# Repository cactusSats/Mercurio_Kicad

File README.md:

# Mercúrio_Kicad
Kicad, Gerbers e arquivos Flatcam do satélite mercúrio

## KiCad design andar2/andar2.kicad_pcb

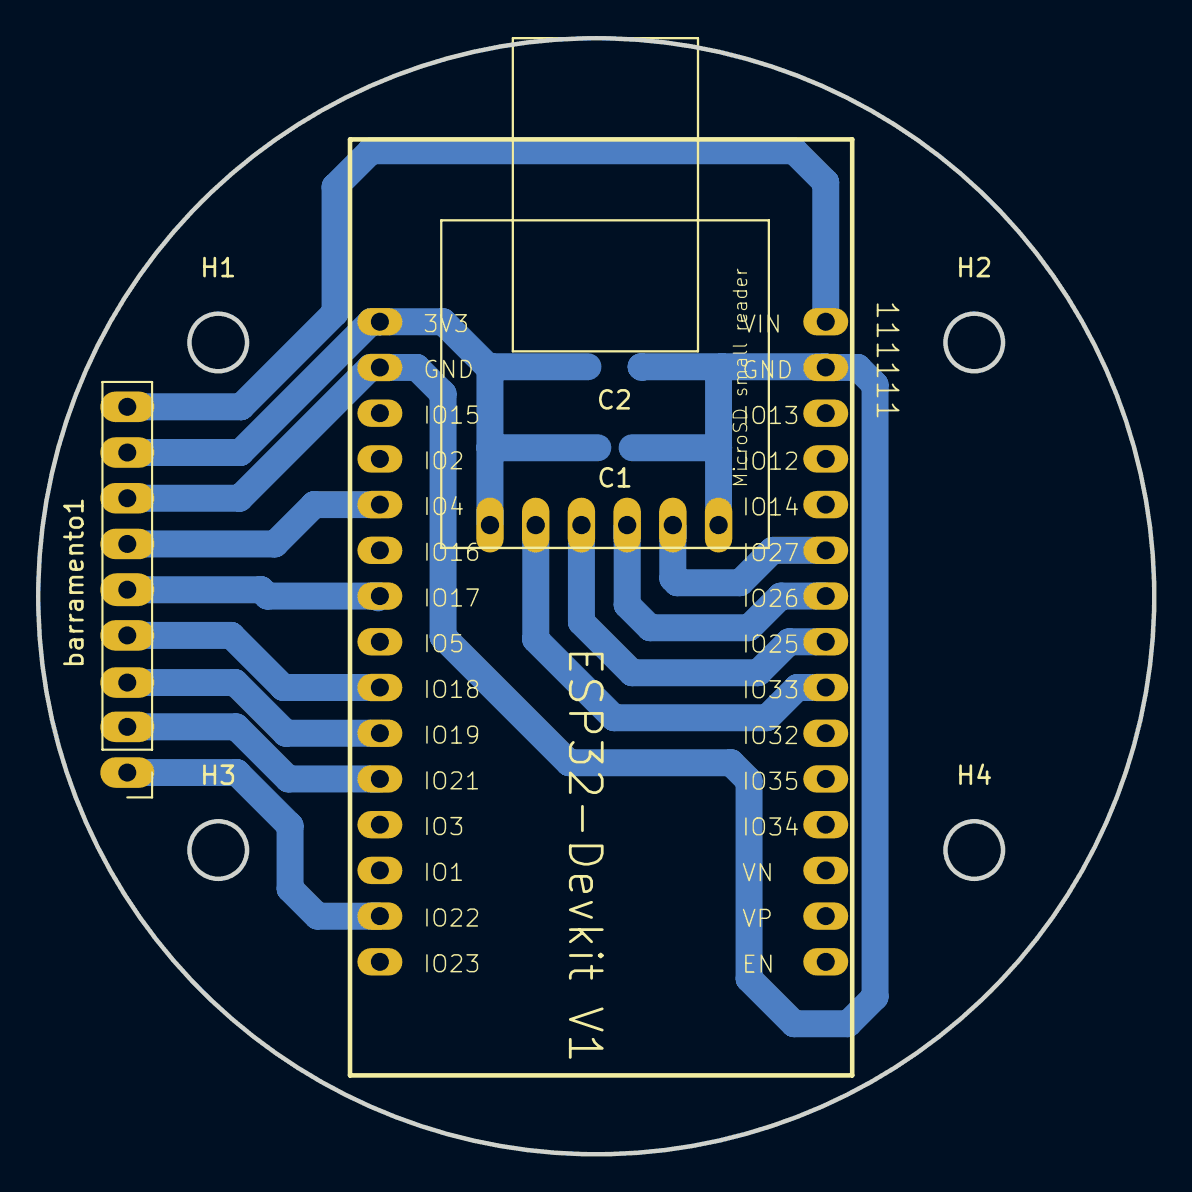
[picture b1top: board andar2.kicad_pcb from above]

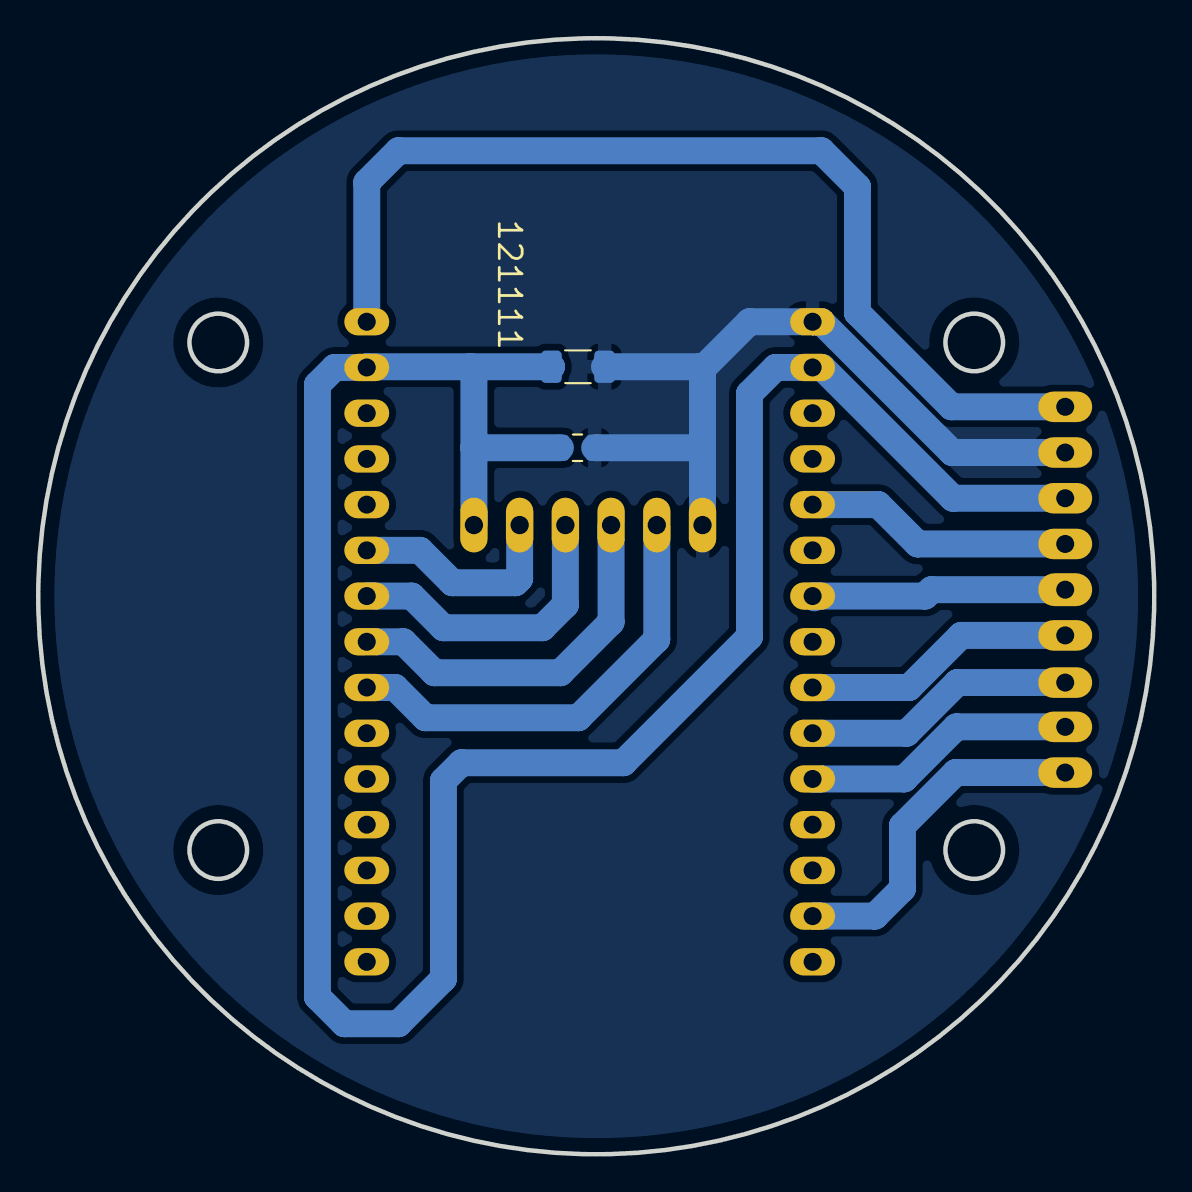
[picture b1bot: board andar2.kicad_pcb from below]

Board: 2 copper layers, 62.0 x 62.0 mm, 9 parts (2 on the bottom side), 13 nets.

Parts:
111111: ESP32-DEVKITV1
121111: MICROSD_SMALL_READER_FOOTPRINT
C1: 100nF; C_0805_2012Metric
C2: 10uF; C_1206_3216Metric
H1, H2, H3, H4: MountingHole; MountingHole_3.2mm_M3
barramento1: Conn_01x09; PinHeader_1x09_P2.54mm_Vertical

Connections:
3V3: 111111.1 (3V3), 121111.3V3, C1.1, C2.1, barramento1.8
CS: 111111.22 (IO33), 121111.CS
GND: 111111.2 (GND), 111111.29 (GND1), 121111.GND, C1.2, C2.2, barramento1.7
I2C_SCL: 111111.5 (IO4), barramento1.6
I2C_SDA: 111111.7 (IO17), barramento1.5
I2S_BCLK: 111111.11 (IO21), barramento1.2
I2S_SD: 111111.14 (IO22), barramento1.1
I2S_WS: 111111.10 (IO19), barramento1.3
MISO: 111111.25 (IO26), 121111.MISO
MOSI: 111111.23 (IO25), 121111.MOSI
ONEWIRE_DATA: 111111.9 (IO18), barramento1.4
SPI_CLK: 111111.24 (IO27), 121111.CLK
VIN: 111111.30 (VIN), barramento1.9

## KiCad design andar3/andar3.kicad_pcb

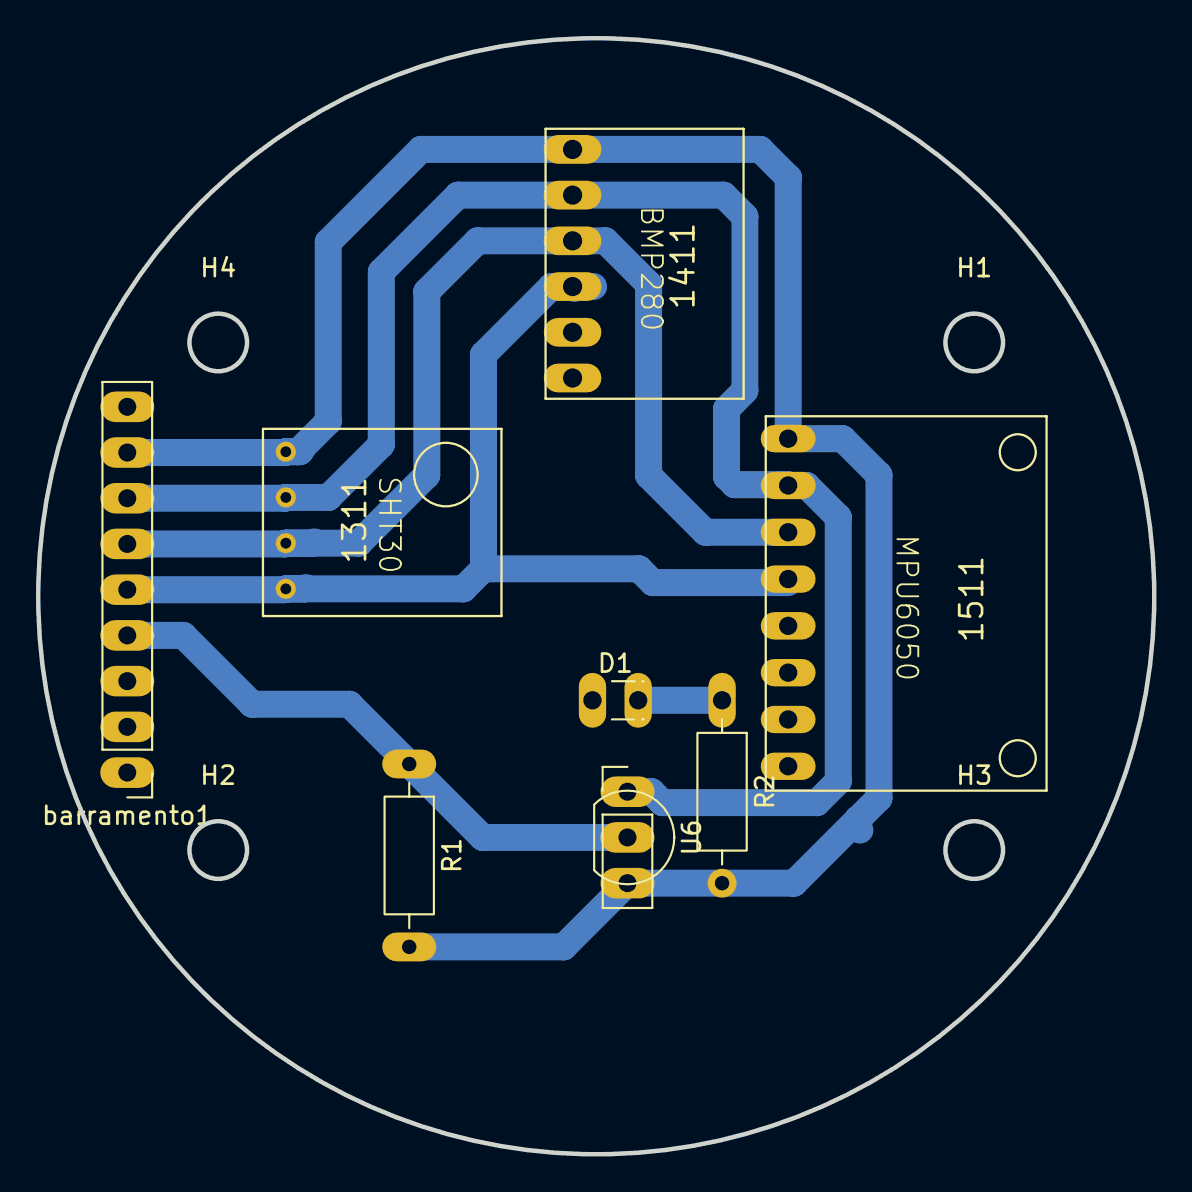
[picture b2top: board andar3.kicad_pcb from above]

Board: 2 copper layers, 62.0 x 62.0 mm, 12 parts (0 on the bottom side), 6 nets.

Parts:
1311: SHT30_FOOTPRINT
1411: BMP280_FOOTPRINT
1511: MPU6050_FOOTPRINT
D1: LED; LED_Rectangular_W3.0mm_H2.0mm
H1, H2, H3, H4: MountingHole; MountingHole_3.2mm_M3
R1: 4.7K; R_Axial_DIN0207_L6.3mm_D2.5mm_P10.16mm_Horizontal
R2: 220; R_Axial_DIN0207_L6.3mm_D2.5mm_P10.16mm_Horizontal
U6: DS18B20; TO-92_Inline
barramento1: Conn_01x09; PinHeader_1x09_P2.54mm_Vertical

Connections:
3V3: 1311.VIN, 1411.VCC, 1511.VCC, R1.2, R2.2, U6.3 (V_{DD}), barramento1.8
GND: 1311.GND, 1411.GND, 1511.GND, D1.1 (K), U6.1 (GND), barramento1.7
I2C_SCL: 1311.SCL, 1411.SCL, 1511.SCL, barramento1.6
I2C_SDA: 1311.SDA, 1411.SDA, 1511.SDA, barramento1.5
unnamed: D1.2 (A), R2.1
ONEWIRE_DATA: R1.1, U6.2 (DQ), barramento1.4

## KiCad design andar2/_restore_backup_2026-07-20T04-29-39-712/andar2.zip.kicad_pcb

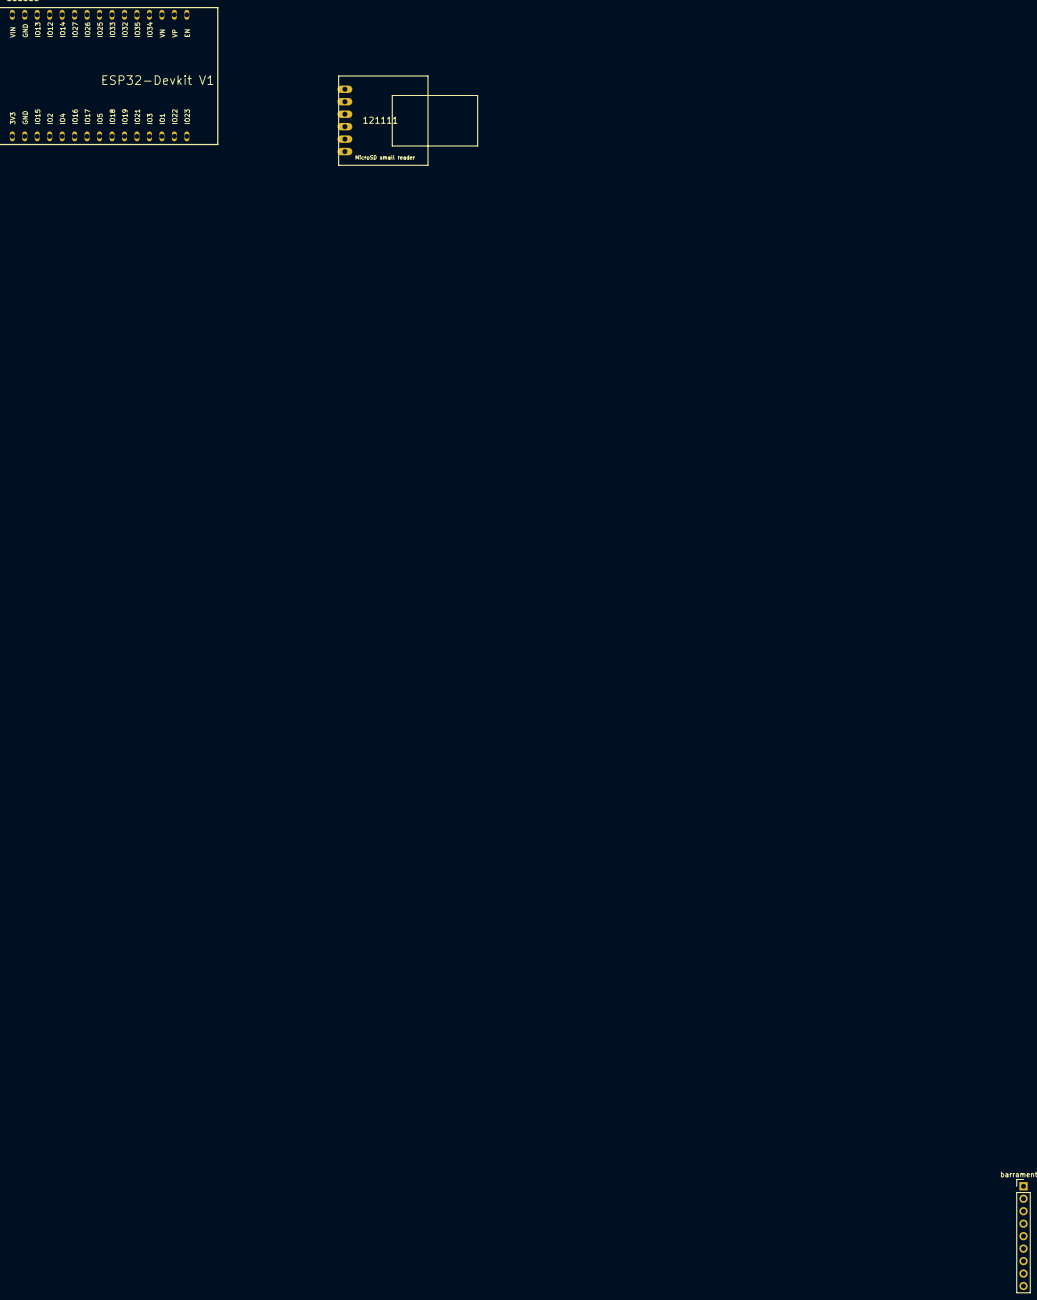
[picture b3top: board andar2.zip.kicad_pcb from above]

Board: 2 copper layers, 7 parts (0 on the bottom side), 12 nets, no tracks yet.

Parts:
111111: ESP32-DEVKITV1
121111: MICROSD_SMALL_READER_FOOTPRINT
H5, H6, H7, H8: MountingHole_Pad; MountingHole_3.2mm_M3
barramento1: Conn_01x09; PinHeader_1x09_P2.54mm_Vertical

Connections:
3V3: 111111.1 (3V3), 121111.3V3, barramento1.8
CS: 111111.8 (IO5), 121111.CS
GND: 111111.2 (GND), 111111.29 (GND1), 121111.GND, barramento1.7
I2C_SCL: 111111.14 (IO22), barramento1.5
I2C_SDA: 111111.11 (IO21), barramento1.6
I2S_BCLK: 111111.25 (IO26), barramento1.3
I2S_SD: 111111.24 (IO27), barramento1.1
I2S_WS: 111111.23 (IO25), barramento1.2
MISO: 111111.10 (IO19), 121111.MISO
MOSI: 111111.15 (IO23), 121111.MOSI
ONEWIRE_DATA: 111111.5 (IO4), barramento1.4
SPI_CLK: 111111.9 (IO18), 121111.CLK

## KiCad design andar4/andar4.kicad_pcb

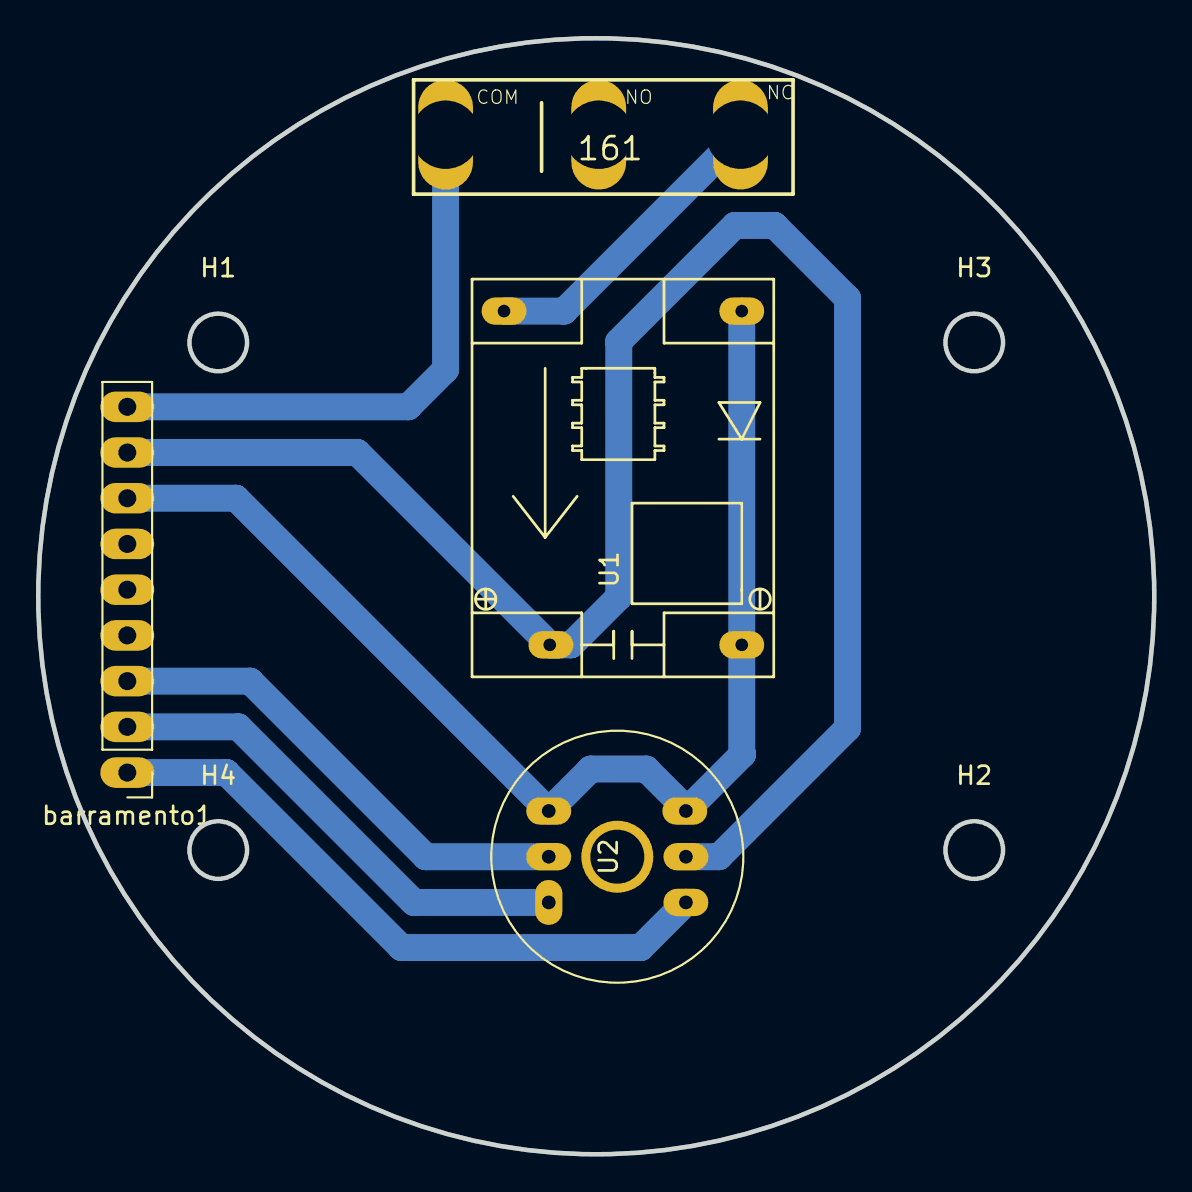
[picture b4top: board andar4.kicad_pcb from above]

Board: 2 copper layers, 62.0 x 62.0 mm, 8 parts (0 on the bottom side), 7 nets.

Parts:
161: CHAVESS-5GL
H1, H2, H3, H4: MountingHole; MountingHole_3.2mm_M3
U1: MP1584_buck_module
U2: INMP441; inmp441
barramento1: Conn_01x09; PinHeader_1x09_P2.54mm_Vertical

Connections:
3V3: U1.4 (out+1), U2.2 (VDD), barramento1.8
GND: U1.2 (in-1), U1.3 (out-1), U2.1 (GND), U2.4 (L/R), barramento1.7
I2S_BCLK: U2.6 (SCK), barramento1.2
I2S_SD: U2.3 (SD), barramento1.1
I2S_WS: U2.5 (WS), barramento1.3
unnamed: 161.P$3, U1.1 (in+1)
VIN: 161.P$1, barramento1.9

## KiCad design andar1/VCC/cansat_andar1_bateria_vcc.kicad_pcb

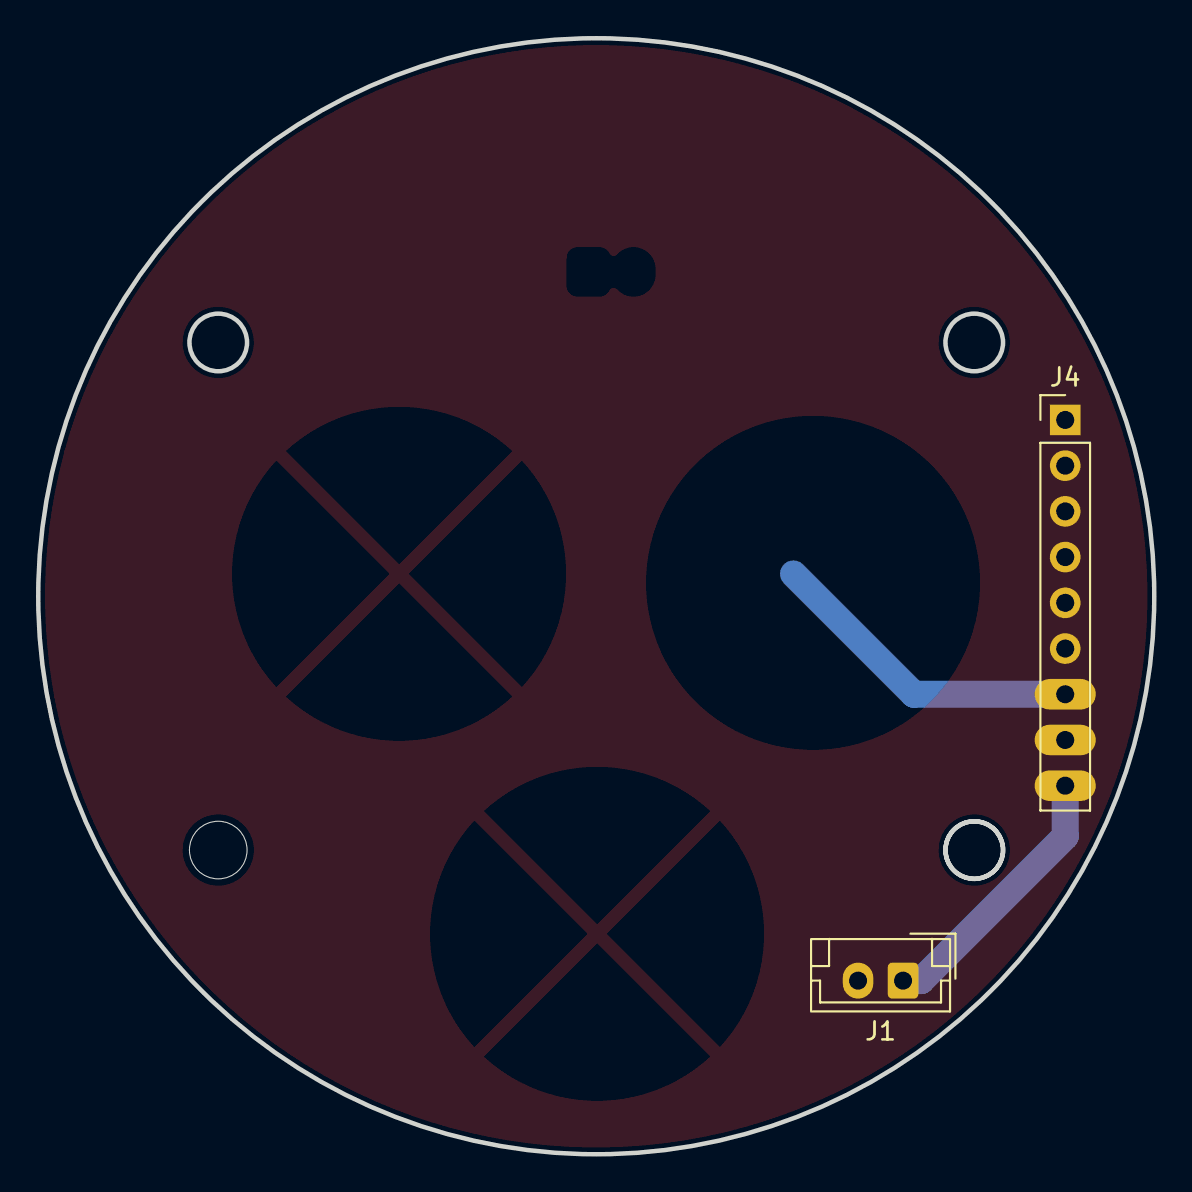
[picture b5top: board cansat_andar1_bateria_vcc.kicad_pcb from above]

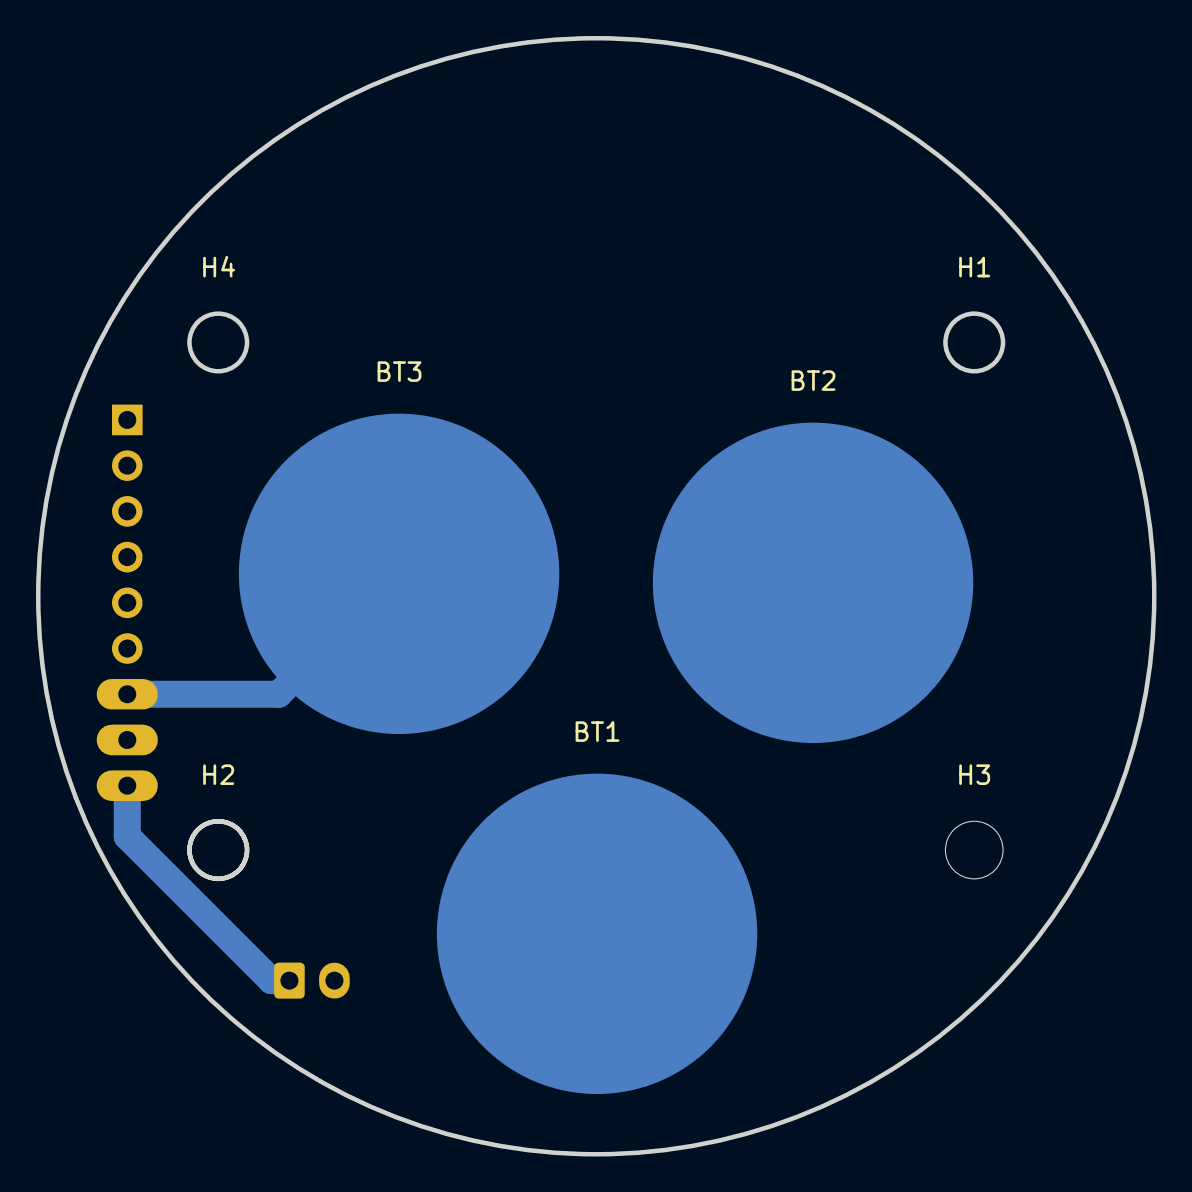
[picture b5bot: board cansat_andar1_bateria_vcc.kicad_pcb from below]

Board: 2 copper layers, 62.0 x 62.0 mm, 9 parts (7 on the bottom side), 3 nets.

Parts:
BT1, BT2, BT3: Battery_Cell; BatteryHolder_18650_em_pe
H1, H2, H3, H4: MountingHole; MountingHole_3.2mm_M3
J1: Conn_01x02; JST_EH_B2B-EH-A_1x02_P2.50mm_Vertical
J4: Conn_01x09; PinHeader_1x09_P2.54mm_Vertical

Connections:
GND: BT1.2 (-_2), BT3.2 (-_2)
unnamed: BT2.2 (-_2), J4.7
unnamed: J1.1 (Pin_1_1), J4.9

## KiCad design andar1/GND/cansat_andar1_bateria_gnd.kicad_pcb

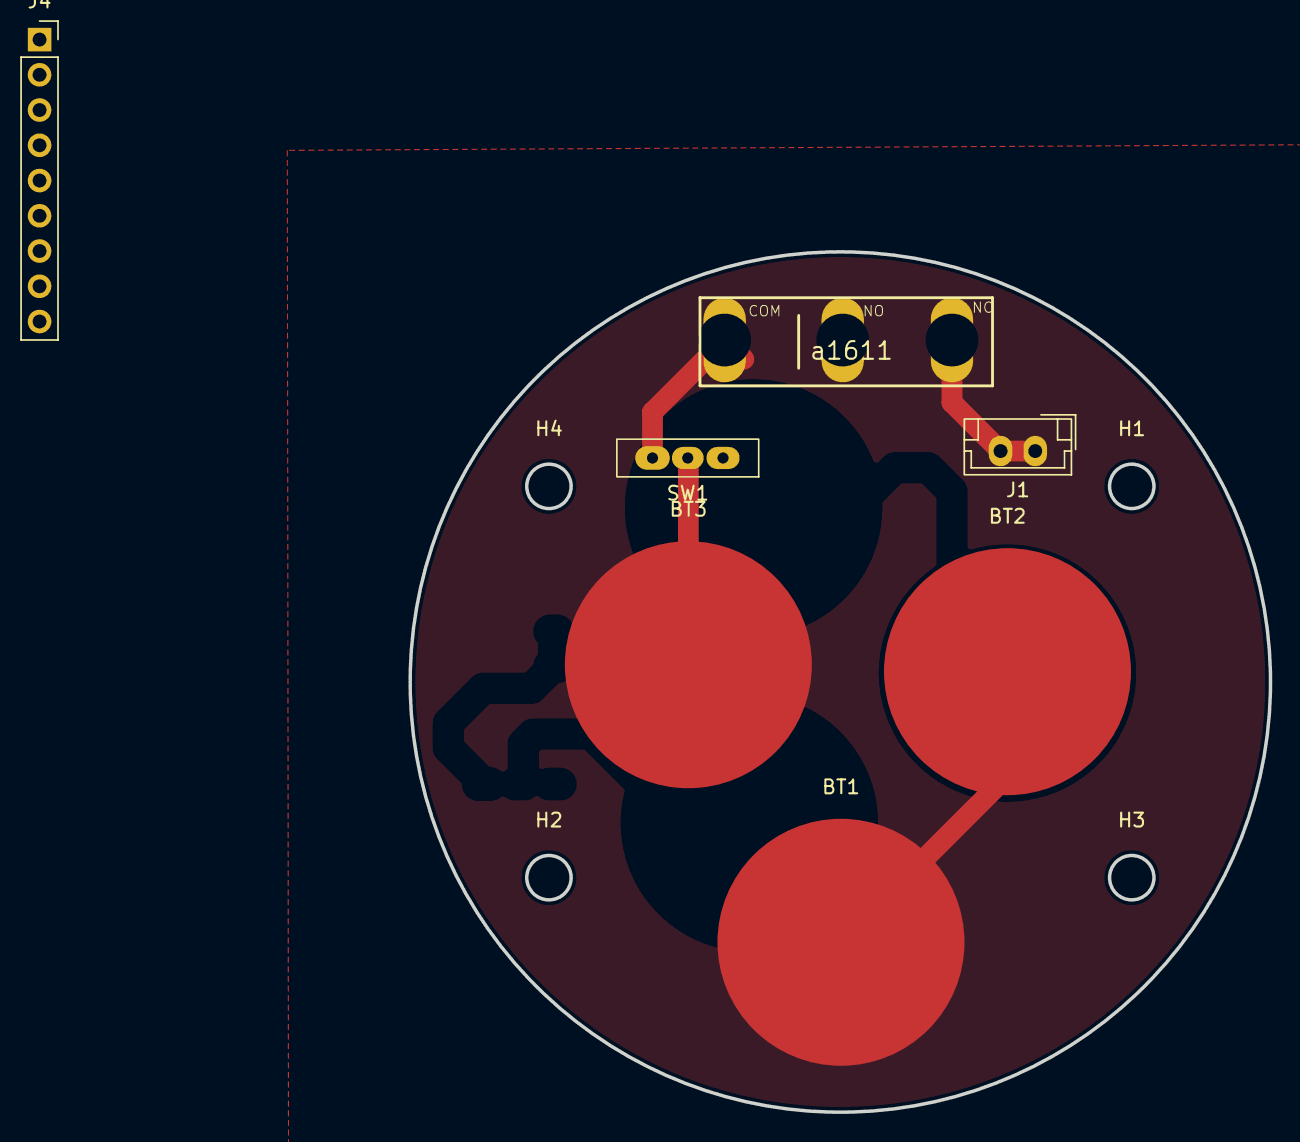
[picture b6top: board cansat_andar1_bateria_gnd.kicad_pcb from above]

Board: 2 copper layers, 62.0 x 62.0 mm, 15 parts (0 on the bottom side), 2 nets.

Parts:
BT1, BT2, BT3: Battery_Cell; BatteryHolder_18650_em_pe
H1, H2, H3#2, H4: MountingHole_Pad; MountingHole_3.2mm_M3
H1#2, H2#2, H3, H4#2: MountingHole; MountingHole_3.2mm_M3
J1: Conn_01x02; JST_EH_B2B-EH-A_1x02_P2.50mm_Vertical
J4: Conn_01x09; PinSocket_1x09_P2.54mm_Vertical
SW1: SW_Wuerth_450301014042; SW_Slide-03_Wuerth-WS-SLTV_10x2.5x6.4_P2.54mm
a1611: CHAVESS-5GL

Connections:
GND: BT1.2 (-_2), BT2.2 (-_2), BT3.2 (-_2), J1.1, J1.2, J4.1, J4.2, SW1.1 (B), a1611.P$3
unnamed: SW1.3 (A), a1611.P$1
